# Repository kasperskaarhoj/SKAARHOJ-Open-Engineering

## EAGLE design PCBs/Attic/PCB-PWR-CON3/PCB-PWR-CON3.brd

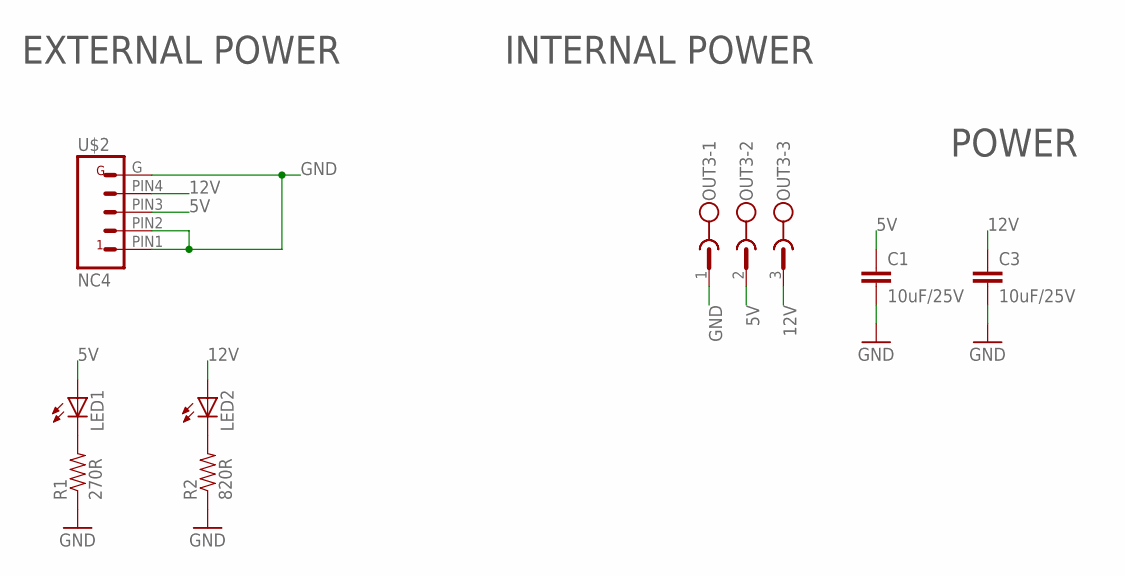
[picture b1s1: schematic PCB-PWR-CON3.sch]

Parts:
C1, C3: 10uF/25V; 0805
LED1, LED2: LED3MM
OUT3: CON1; MSTBV3
R1: 270R; 0603-RES
R2: 820R; 0603-RES
U$2: NC4; NC4-MD-L1

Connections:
5V: C1.1, LED1.A, OUT3.2, U$2.PIN3 (3)
12V: C3.1, LED2.A, OUT3.3, U$2.PIN4 (4)
GND: C1.2, C3.2, OUT3.1, R1.1, R2.1, U$2.G, U$2.PIN1 (1), U$2.PIN2 (2)
unnamed: LED1.K (C), R1.2
unnamed: LED2.K (C), R2.2

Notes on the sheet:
POWER
INTERNAL POWER
EXTERNAL POWER

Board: 2 copper layers, 8 parts (2 on the bottom side), 5 nets, no tracks yet.

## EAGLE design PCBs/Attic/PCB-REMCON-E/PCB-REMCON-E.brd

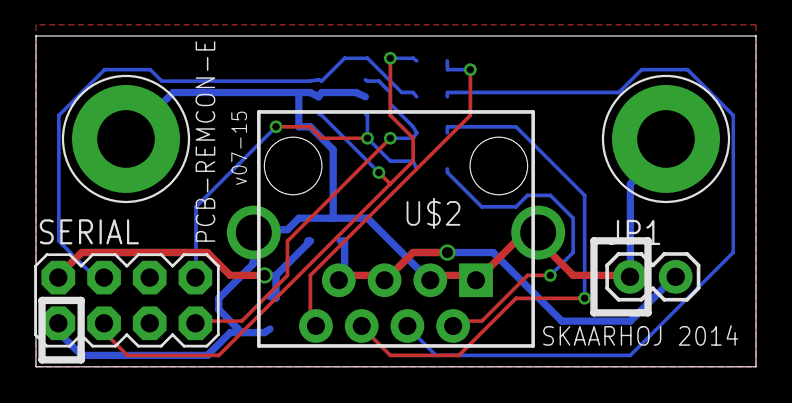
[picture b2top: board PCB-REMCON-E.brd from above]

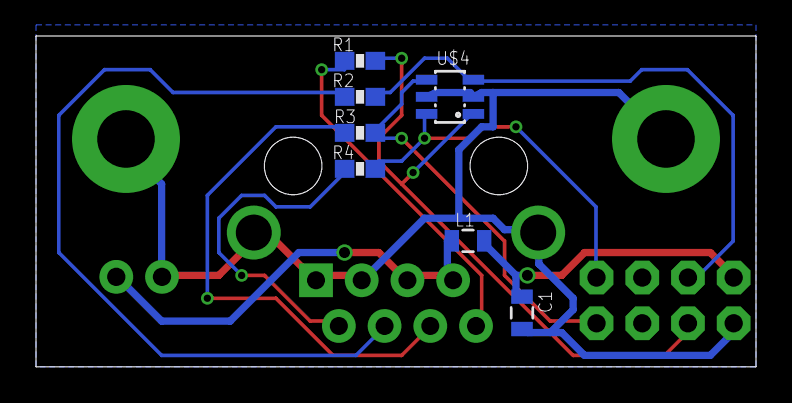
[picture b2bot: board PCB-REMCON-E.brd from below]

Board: 2 copper layers, 40.0 x 18.4 mm, 12 parts (7 on the bottom side), 11 nets.

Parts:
C1: 22uF; 0805
JP1: 1X02
L1: 0805
R1, R2, R3, R4: 50R; 0603-RES
SERIAL: M04X2; 2X4
U$2: RJ45-8_GND
U$3, U$20: GNDPAD6MM; 3.2MMPAD6MM
U$4: TVS_DIODE_ARRAY4; SOT23-6L

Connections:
5V: C1.1, L1.2, SERIAL.2
GND: C1.2, JP1.1, SERIAL.1, U$2.1, U$2.3, U$2.GND, U$2.GND1, U$3.P$1, U$4.2, U$4.5, U$20.P$1
I2C_SCL: R2.2, SERIAL.4, U$4.3
I2C_SCL_IN: R2.1, U$2.4
I2C_SDA: R1.2, SERIAL.3, U$4.1
I2C_SDA_IN: R1.1, U$2.8
unnamed: JP1.2, L1.1, U$2.5, U$2.7
SPI_MOSI: R4.2, SERIAL.8, U$4.6
SPI_MOSI_IN: R4.1, U$2.2
SPI_SCLK: R3.2, SERIAL.7, U$4.4
SPI_SCLK_IN: R3.1, U$2.6

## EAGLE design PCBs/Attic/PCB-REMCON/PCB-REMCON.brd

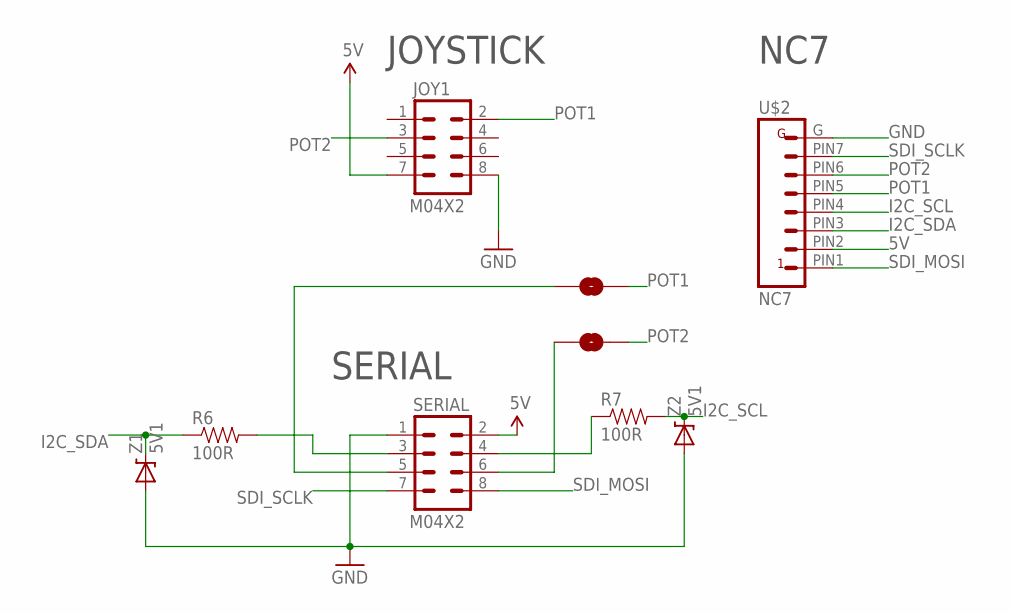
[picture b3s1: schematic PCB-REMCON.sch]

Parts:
JOY1: M04X2; 2X4
R6, R7: 100R; 0603-RES
SCLK->D1, SCLK->D5: SOLDERJUMPERNC; SJ_2S
SERIAL: M04X2; 2X4
U$2: NC7; NC7-MD-L1
Z1, Z2: 5V1; DIODE-ZENER

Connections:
5V: JOY1.7, SERIAL.2, U$2.PIN2 (2)
GND: JOY1.8, SERIAL.1, U$2.G, Z1.P$2 (A), Z2.P$2 (A)
I2C_SCL: R7.2, U$2.PIN4 (4), Z2.P$1 (C)
I2C_SDA: R6.1, U$2.PIN3 (3), Z1.P$1 (C)
unnamed: R6.2, SERIAL.3
unnamed: SCLK->D5.1, SERIAL.6
unnamed: SCLK->D1.1, SERIAL.5
unnamed: R7.1, SERIAL.4
POT1: JOY1.2, SCLK->D1.2, U$2.PIN5 (5)
POT2: JOY1.3, SCLK->D5.2, U$2.PIN6 (6)
SDI_MOSI: SERIAL.8, U$2.PIN1 (1)
SDI_SCLK: SERIAL.7, U$2.PIN7 (7)

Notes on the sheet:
NC7
JOYSTICK
SERIAL

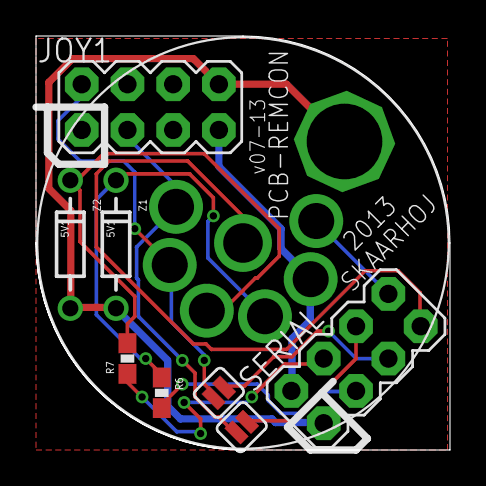
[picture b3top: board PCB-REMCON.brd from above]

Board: 2 copper layers, 23.0 x 23.0 mm, 9 parts (0 on the bottom side), 12 nets.

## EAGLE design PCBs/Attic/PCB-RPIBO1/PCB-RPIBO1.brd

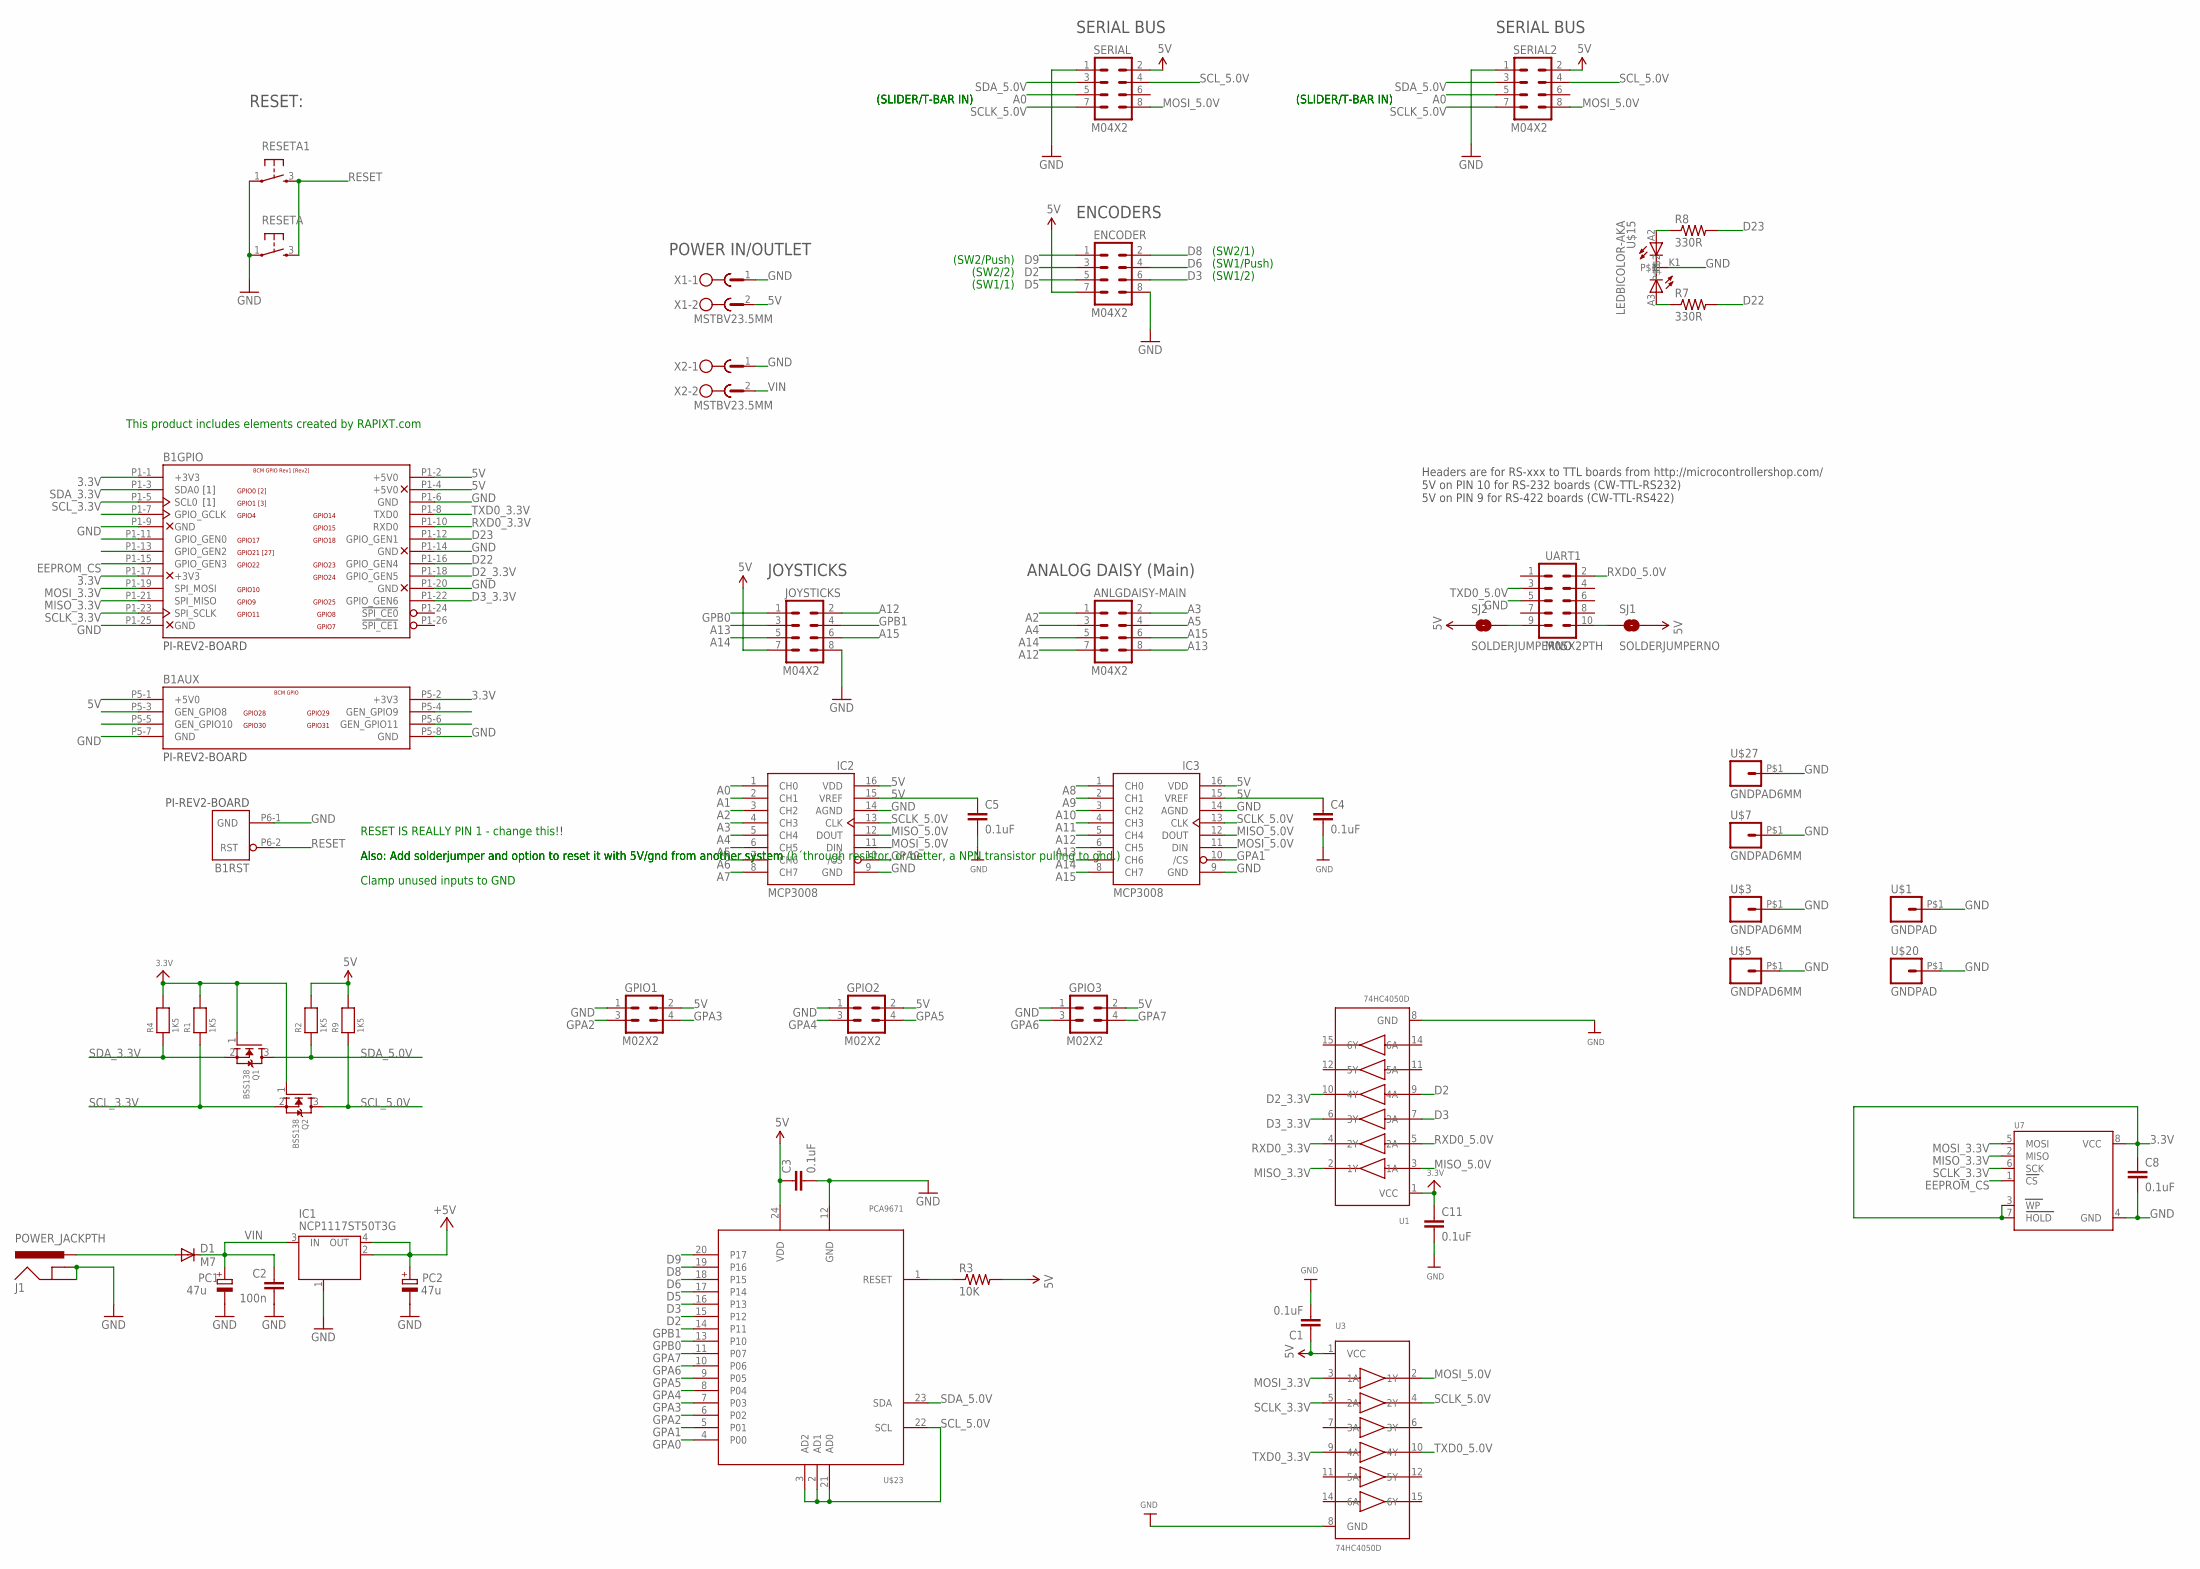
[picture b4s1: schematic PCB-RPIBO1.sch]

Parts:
ANLGDAISY-MAIN: M04X2; 2X4
B1: PI-REV2-BOARD; RASPBERRY-PI-REV2
C1, C3, C4, C5, C8, C11: 0.1uF; 0603-CAP
C2: 100n; C0603-ROUND
D1: M7; SMB
ENCODER: M04X2; 2X4
GPIO1, GPIO2, GPIO3: M02X2; 2X2
IC1: NCP1117ST50T3G; SOT223
IC2, IC3: MCP3008SOIC; SOIC16
J1: POWER_JACKPTH; POWER_JACK_PTH
JOYSTICKS: M04X2; 2X4
PC1, PC2: 47u; PANASONIC_D
Q1, Q2: BSS138; SOT23-WIDE
R1, R2, R4, R9: 1K5; 0603
R3: 10K; 0603-RES
R7, R8: 330R; 0603-RES
RESETA, RESETA1: TAC_SWITCH; PUSHBUTTON
SERIAL, SERIAL2: M04X2; 2X4
SJ1, SJ2: SOLDERJUMPERNO; SJ_2S-NO
U1, U3: 74HC4050D; TSSOP16
U7: EEPROM_SPI_AT25040ATSSOP; TSSOP8-4.4MM
U$1, U$20: GNDPAD; 3.2MMPAD
U$3, U$5, U$7, U$27: GNDPAD6MM; 3.2MMPAD6MM
U$15: LEDBICOLOR-AKA; LED5MM-BICOLOR
U$23: PCA9671; TSSOP24
UART1: M05X2PTH; AVR_ICSP
X1, X2: MSTBV23.5MM; MSTBV2-3.5

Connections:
3.3V: B1.P1-1 (+3V3), B1.P1-17 (+3V3), B1.P5-2 (+3V3), C8.1, C11.1, Q1.1 (G), Q2.1 (G), R1.2, R4.2, U1.1 (VCC), U7.3 (WP), U7.7 (HOLD), U7.8 (VCC)
5V: B1.P1-2 (+5V0), B1.P1-4 (+5V0), B1.P5-1 (+5V0), C1.1, C3.1, C4.1, C5.1, ENCODER.7, GPIO1.2, GPIO2.2, GPIO3.2, IC1.2 (OUT), IC1.4 (OUT), IC2.15 (VREF), IC2.16 (VDD), IC3.15 (VREF), IC3.16 (VDD), JOYSTICKS.7, PC2.+, R2.2, R3.2, R9.2, SERIAL.2, SERIAL2.2, SJ1.2, SJ2.1, U3.1 (VCC), U$23.24 (VDD), X1.2
12V: D1.A, J1.PWR
A0: IC2.1 (CH0), SERIAL.5, SERIAL2.5
A1: IC2.2 (CH1)
A2: ANLGDAISY-MAIN.1, IC2.3 (CH2)
A3: ANLGDAISY-MAIN.2, IC2.4 (CH3)
A4: ANLGDAISY-MAIN.3, IC2.5 (CH4)
A5: ANLGDAISY-MAIN.4, IC2.6 (CH5)
A6: IC2.7 (CH6)
A7: IC2.8 (CH7)
A8: IC3.1 (CH0)
A9: IC3.2 (CH1)
A10: IC3.3 (CH2)
A11: IC3.4 (CH3)
A12: ANLGDAISY-MAIN.7, IC3.5 (CH4), JOYSTICKS.2
A13: ANLGDAISY-MAIN.8, IC3.6 (CH5), JOYSTICKS.3
A14: ANLGDAISY-MAIN.5, IC3.7 (CH6), JOYSTICKS.5
A15: ANLGDAISY-MAIN.6, IC3.8 (CH7), JOYSTICKS.6
D2: ENCODER.3, U1.9 (4A), U$23.15 (P12)
D2_3.3V: B1.P1-18 (GPIO_GEN5), U1.10 (4Y)
D3: ENCODER.6, U1.7 (3A), U$23.16 (P13)
D3_3.3V: B1.P1-22 (GPIO_GEN6), U1.6 (3Y)
D5: ENCODER.5, U$23.17 (P14)
D6: ENCODER.4, U$23.18 (P15)
D8: ENCODER.2, U$23.19 (P16)
D9: ENCODER.1, U$23.20 (P17)
D22: B1.P1-16 (GPIO_GEN4), R7.2
D23: B1.P1-12 (GPIO_GEN1), R8.2
EEPROM_CS: B1.P1-15 (GPIO_GEN3), U7.1 (CS)
GND: B1.P1-6 (GND), B1.P1-9 (GND), B1.P1-14 (GND), B1.P1-20 (GND), B1.P1-25 (GND), B1.P5-7 (GND), B1.P5-8 (GND), B1.P6-1 (GND), C1.2, C2.2, C3.2, C4.2, C5.2, C8.2, C11.2, ENCODER.8, GPIO1.1, GPIO2.1, GPIO3.1, IC1.1 (GND/ADJ), IC2.9 (GND), IC2.14 (AGND), IC3.9 (GND), IC3.14 (AGND), J1.GND, J1.SHUNT (GNDBREAK), JOYSTICKS.8, PC1.-, PC2.-, RESETA.1, RESETA1.1, SERIAL.1, SERIAL2.1, U1.8 (GND), U3.8 (GND), U7.4 (GND), U$1.P$1, U$3.P$1, U$5.P$1, U$7.P$1, U$15.K1, U$20.P$1, U$23.12 (GND), U$27.P$1, UART1.5, X1.1, X2.1
GPA0: IC2.10 (/CS), U$23.4 (P00)
GPA1: IC3.10 (/CS), U$23.5 (P01)
GPA2: GPIO1.3, U$23.6 (P02)
GPA3: GPIO1.4, U$23.7 (P03)
GPA4: GPIO2.3, U$23.8 (P04)
GPA5: GPIO2.4, U$23.9 (P05)
GPA6: GPIO3.3, U$23.10 (P06)
GPA7: GPIO3.4, U$23.11 (P07)
GPB0: JOYSTICKS.1, U$23.13 (P10)
GPB1: JOYSTICKS.4, U$23.14 (P11)
MISO_3.3V: B1.P1-21 (SPI_MISO), U1.2 (1Y), U7.2 (MISO)
MISO_5.0V: IC2.12 (DOUT), IC3.12 (DOUT), U1.3 (1A)
MOSI_3.3V: B1.P1-19 (SPI_MOSI), U3.3 (1A), U7.5 (MOSI)
MOSI_5.0V: IC2.11 (DIN), IC3.11 (DIN), SERIAL.8, SERIAL2.8, U3.2 (1Y)
unnamed: R3.1, U$23.1 (RESET)
unnamed: SJ2.2, UART1.9
unnamed: SJ1.1, UART1.10
unnamed: R8.1, U$15.A2
unnamed: R7.1, U$15.A3
RESET: B1.P6-2 (RST), RESETA.3, RESETA1.3
RXD0_3.3V: B1.P1-10 (RXD0), U1.4 (2Y)
RXD0_5.0V: U1.5 (2A), UART1.2
SCLK_3.3V: B1.P1-23 (SPI_SCLK), U3.5 (2A), U7.6 (SCK)
SCLK_5.0V: IC2.13 (CLK), IC3.13 (CLK), SERIAL.7, SERIAL2.7, U3.4 (2Y)
SCL_3.3V: B1.P1-5 (SCL0), Q2.2 (S), R1.1
SCL_5.0V: Q2.3 (D), R9.1, SERIAL.4, SERIAL2.4, U$23.2 (AD1), U$23.3 (AD2), U$23.21 (AD0), U$23.22 (SCL)
SDA_3.3V: B1.P1-3 (SDA0), Q1.2 (S), R4.1
SDA_5.0V: Q1.3 (D), R2.1, SERIAL.3, SERIAL2.3, U$23.23 (SDA)
TXD0_3.3V: B1.P1-8 (TXD0), U3.9 (4A)
TXD0_5.0V: U3.10 (4Y), UART1.3
VIN: C2.1, D1.C, IC1.3 (IN), PC1.+, X2.2

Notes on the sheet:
JOYSTICKS
Headers are for RS-xxx to TTL boards from http://microcontrollershop.com/ 5V on PIN 10 for RS-232 boards (CW-TTL-RS232) 5V on PIN 9 for RS-422 boards (CW-TTL-RS422)
ENCODERS
SERIAL BUS
(SLIDER/T-BAR IN)
(SW2/Push)
(SW2/2)
(SW1/1)
(SW2/1)
(SW1/Push)
(SW1/2)
RESET:
ANALOG DAISY (Main)
This product includes elements created by RAPIXT.com
POWER IN/OUTLET
RESET IS REALLY PIN 1 - change this!!
Also: Add solderjumper and option to reset it with 5V/gnd from another system
Also: Add solderjumper and option to reset it with 5V/gnd from another system (h´through resistor, or better, a NPN transistor pulling to gnd.)
Clamp unused inputs to GND

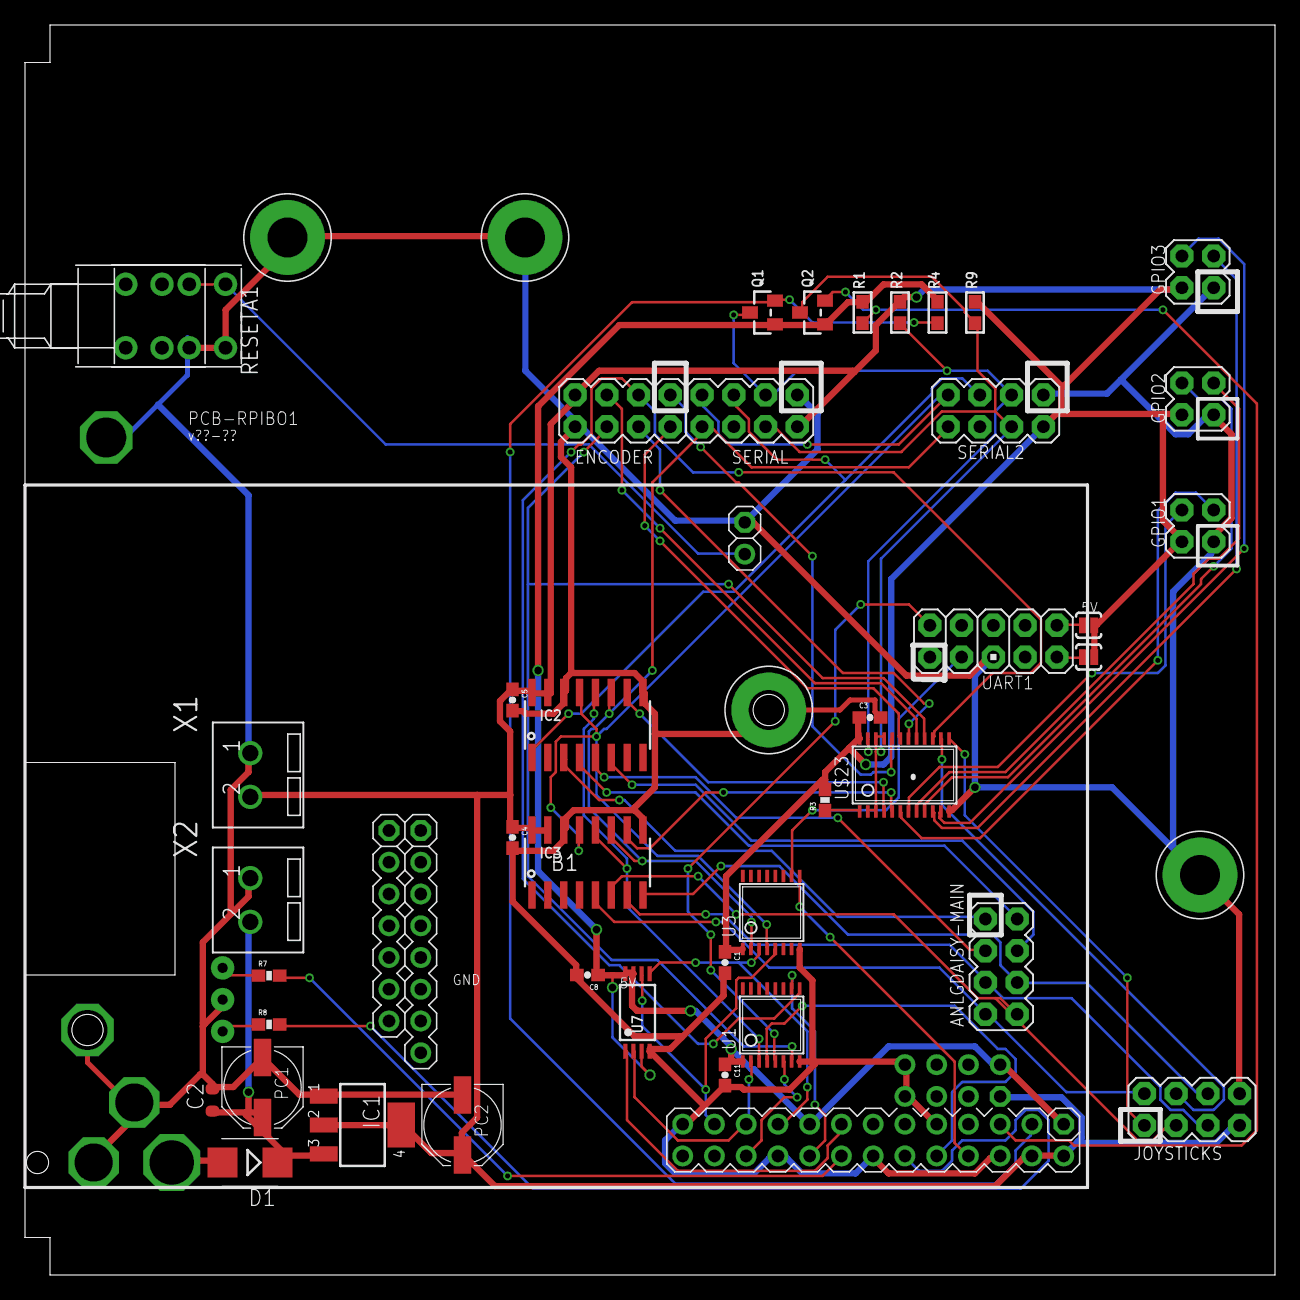
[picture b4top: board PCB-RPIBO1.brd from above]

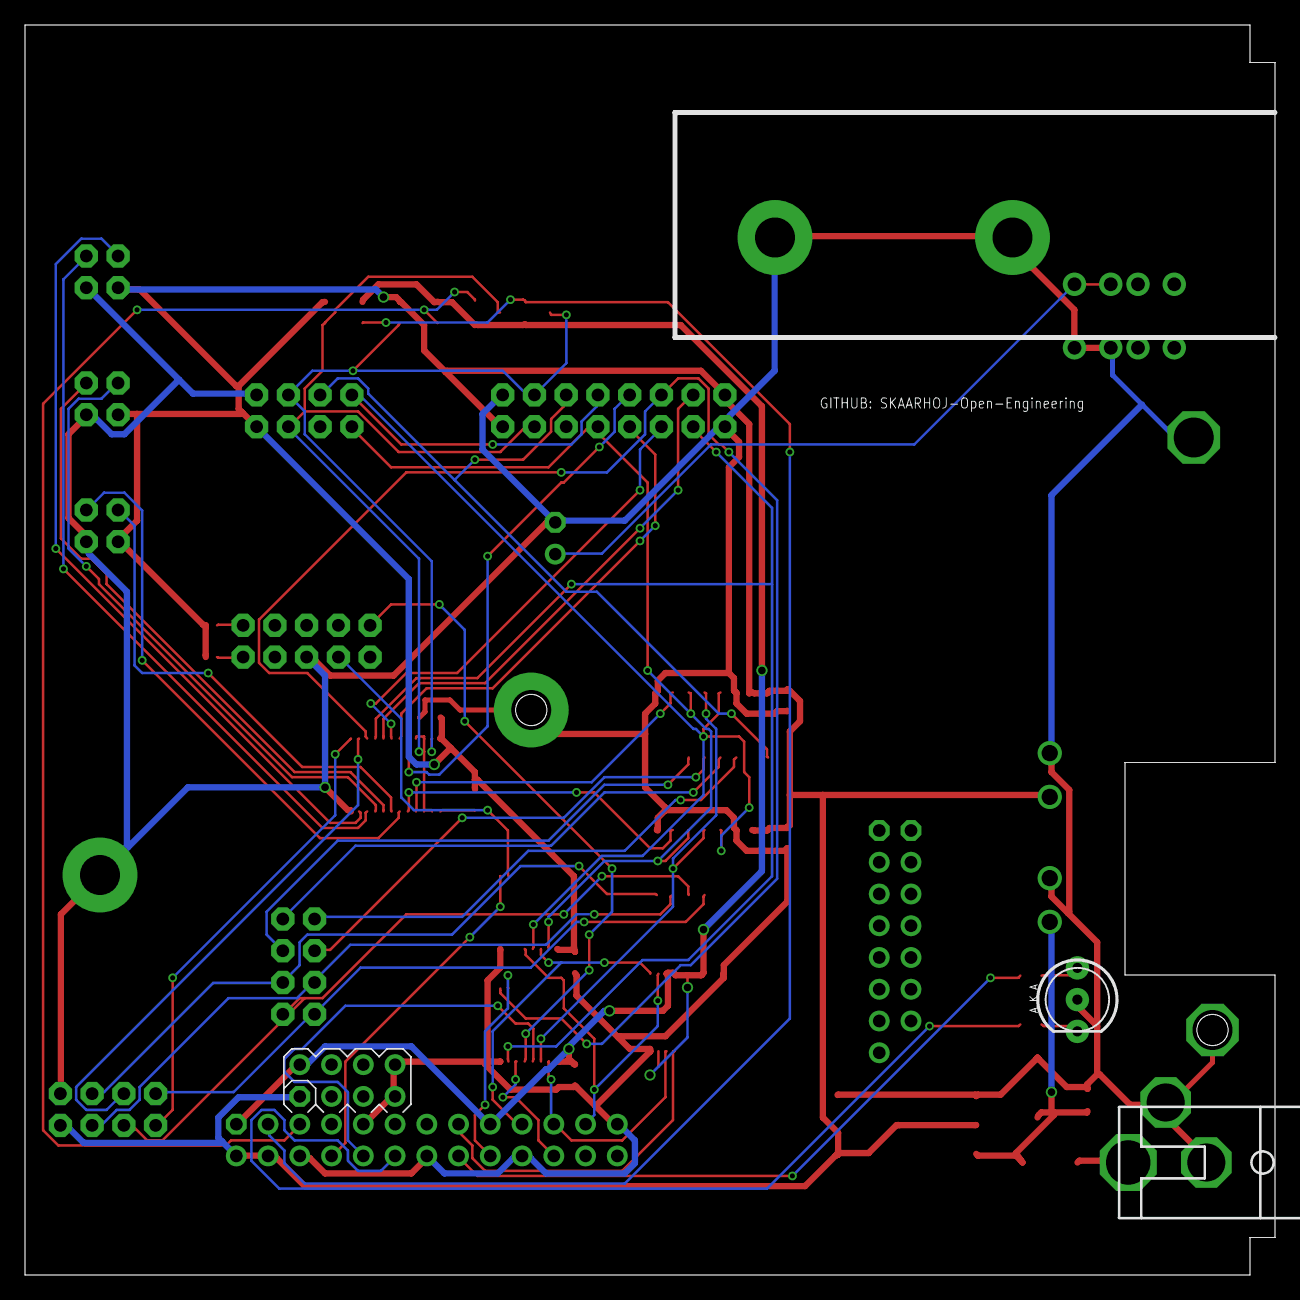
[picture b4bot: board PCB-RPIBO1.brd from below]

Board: 2 copper layers, 100.0 x 100.0 mm, 50 parts (2 on the bottom side), 55 nets.

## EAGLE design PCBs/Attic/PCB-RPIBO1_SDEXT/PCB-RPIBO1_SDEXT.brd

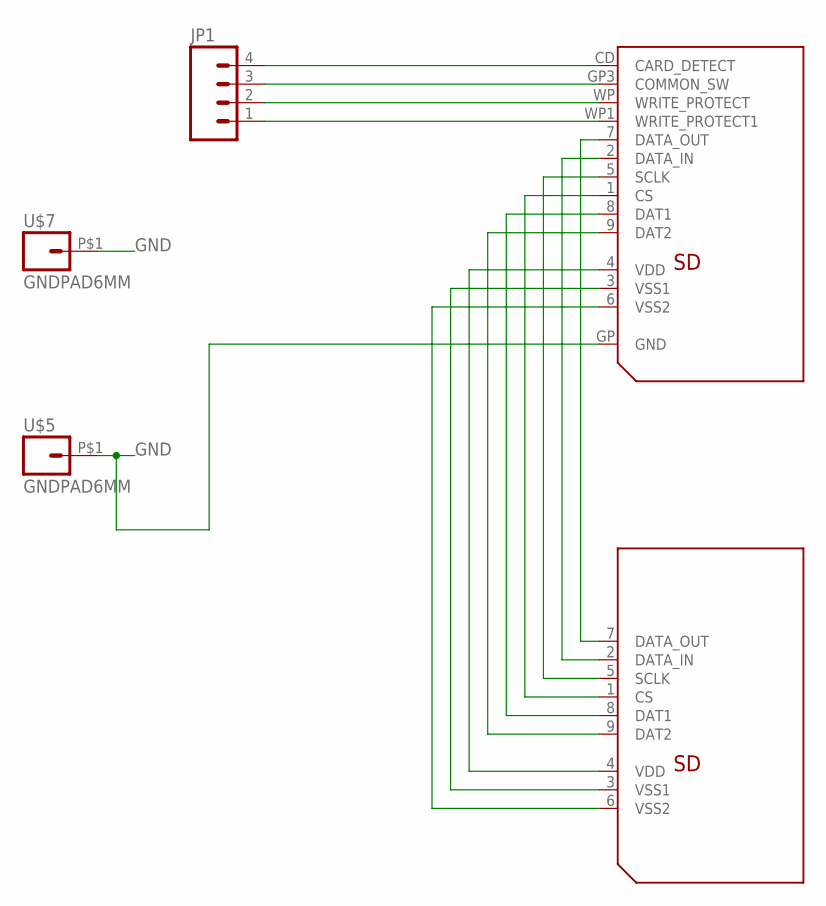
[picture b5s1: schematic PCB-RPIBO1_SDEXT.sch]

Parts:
JP1: M04PTH; 1X04
U$2: SD06132; SD_LARGE
U$4: SDMALEPCB; SD_MALEPCB
U$5, U$7: GNDPAD6MM; 3.2MMPAD6MM

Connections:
GND: U$2.GP (GND), U$5.P$1, U$7.P$1
unnamed: U$2.7 (DATA_OUT), U$4.7 (DATA_OUT)
unnamed: U$2.2 (DATA_IN), U$4.2 (DATA_IN)
unnamed: U$2.5 (SCLK), U$4.5 (SCLK)
unnamed: U$2.1 (CS), U$4.1 (CS)
unnamed: U$2.8 (DAT1), U$4.8 (DAT1)
unnamed: U$2.9 (DAT2), U$4.9 (DAT2)
unnamed: JP1.4, U$2.CD (CARD_DETECT)
unnamed: JP1.3, U$2.GP3 (COMMON_SW)
unnamed: JP1.2, U$2.WP (WRITE_PROTECT)
unnamed: JP1.1, U$2.WP1 (WRITE_PROTECT1)
VDD: U$2.4 (VDD), U$4.4 (VDD)
VSS1: U$2.3 (VSS1), U$4.3 (VSS1)
VSS2: U$2.6 (VSS2), U$4.6 (VSS2)

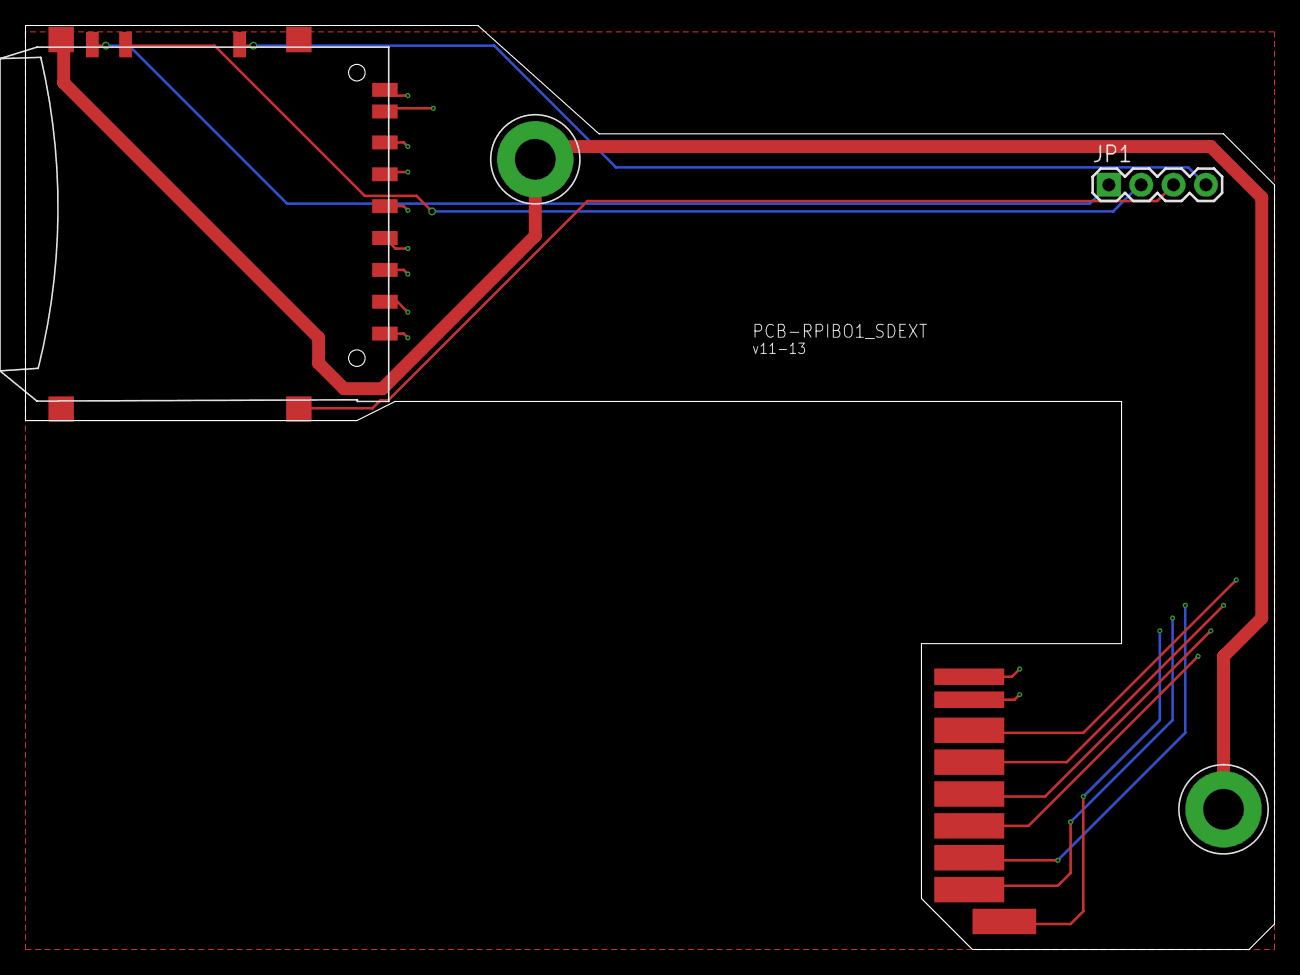
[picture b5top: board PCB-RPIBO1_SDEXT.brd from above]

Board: 4 copper layers, 98.0 x 72.5 mm, 5 parts (1 on the bottom side), 14 nets.

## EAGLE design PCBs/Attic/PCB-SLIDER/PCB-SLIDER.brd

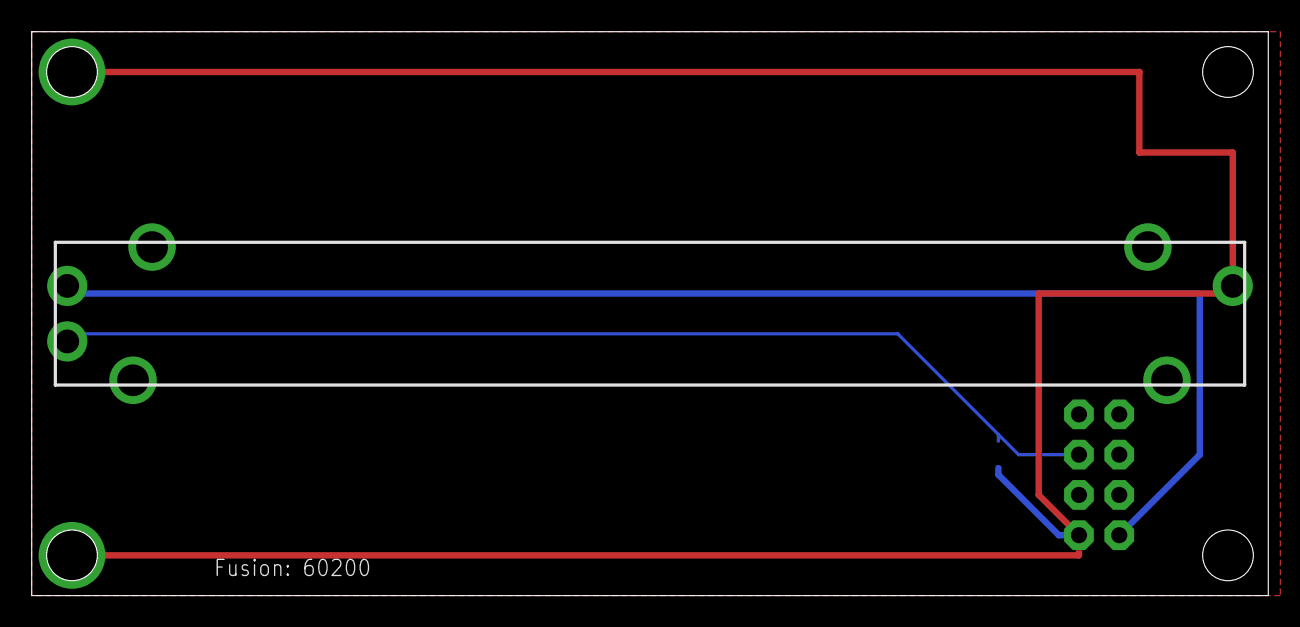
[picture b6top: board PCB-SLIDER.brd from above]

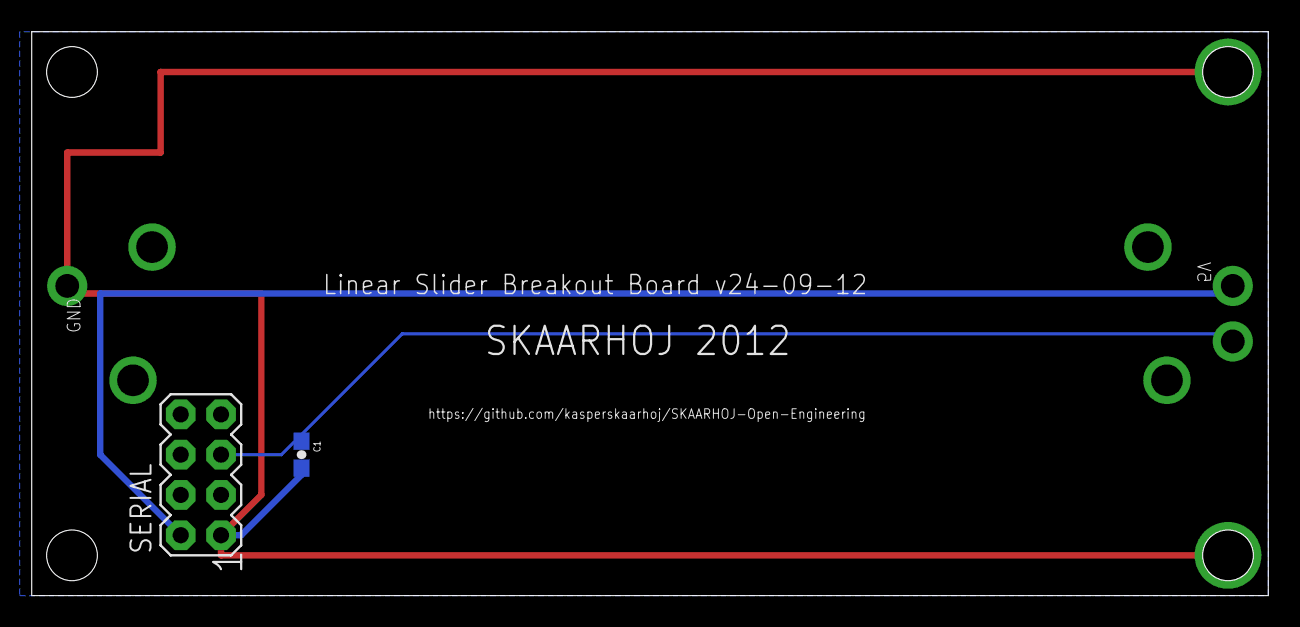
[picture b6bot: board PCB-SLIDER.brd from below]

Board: 2 copper layers, 78.0 x 35.6 mm, 3 parts (2 on the bottom side), 3 nets.

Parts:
C1: 10nF; 0603-CAP
POT1: 10K Linear; SLIDER60
SERIAL: M04X2; 2X4

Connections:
5V: POT1.1, SERIAL.2
GND: C1.2, POT1.3, SERIAL.1
SLIDER_IN: C1.1, POT1.2A, SERIAL.5

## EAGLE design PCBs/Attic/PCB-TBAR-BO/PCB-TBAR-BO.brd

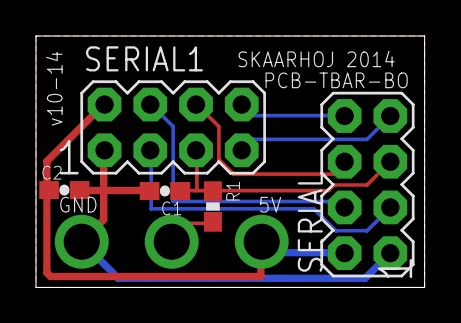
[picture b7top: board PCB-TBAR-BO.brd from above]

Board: 2 copper layers, 21.6 x 14.0 mm, 5 parts (0 on the bottom side), 8 nets.

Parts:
C1: 1uF; 0603-CAP
C2: 10uF; 0603-CAP
R1: 10K; 0603-RES
SERIAL, SERIAL1: M04X2; 2X4

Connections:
5V: C2.1, SERIAL.2, SERIAL1.2
DISP_DATA_OUT: SERIAL.6, SERIAL1.6
GND: C1.2, C2.2, SERIAL.1, SERIAL1.1
I2C_SCL: SERIAL.4, SERIAL1.4
I2C_SDA: SERIAL.3, SERIAL1.3
SDI_MOSI: SERIAL.8, SERIAL1.8
SDI_SCLK: SERIAL.7, SERIAL1.7
SLIDER_IN: C1.1, R1.1, SERIAL.5, SERIAL1.5

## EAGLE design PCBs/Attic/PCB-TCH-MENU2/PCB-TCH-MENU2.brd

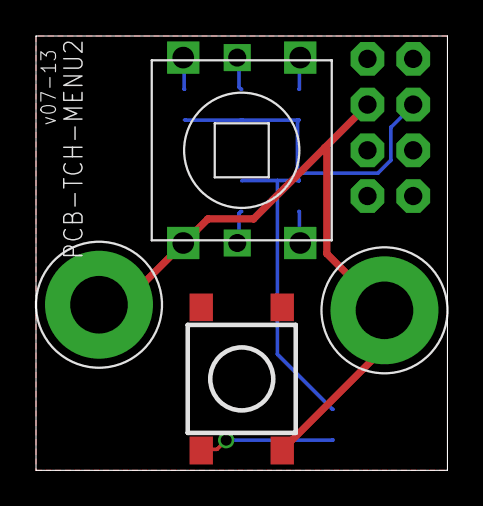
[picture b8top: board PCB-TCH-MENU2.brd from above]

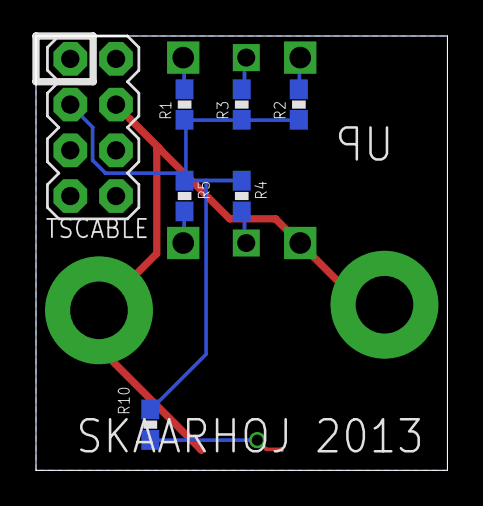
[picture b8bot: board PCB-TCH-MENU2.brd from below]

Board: 2 copper layers, 22.9 x 24.1 mm, 11 parts (7 on the bottom side), 8 nets.

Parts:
MENU: NAV-SWITCH-5WAYCNK_LOCK; NAV-SWITCH-5WAY
R1: 820; 0603-RES
R2: 1K5; 0603-RES
R3: 3K3; 0603-RES
R4: 330; 0603-RES
R5: 2K; 0603-RES
R10: 100R; 0603-RES
S1: SWITCH-MOMENTARY-2; TACTILE_SWITCH_TALL
TSCABLE: M04X2; 2X4
U$15, U$20: GNDPAD6MM; 3.2MMPAD6MM

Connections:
GND: MENU.PIN4, S1.B2, TSCABLE.4, U$15.P$1, U$20.P$1
KEYIN: R1.1, R2.1, R3.1, R4.1, R5.1, R10.1, TSCABLE.3
unnamed: R10.2, S1.A2
unnamed: MENU.PIN1, R1.2
unnamed: MENU.PIN3, R2.2
unnamed: MENU.PIN2, R3.2
unnamed: MENU.PIN5, R4.2
unnamed: MENU.PIN6, R5.2

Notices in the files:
parts and their libraries:
SparkFun: Licensing: CC v3.0 Share-Alike You are welcome to use this library for commercial purposes.
